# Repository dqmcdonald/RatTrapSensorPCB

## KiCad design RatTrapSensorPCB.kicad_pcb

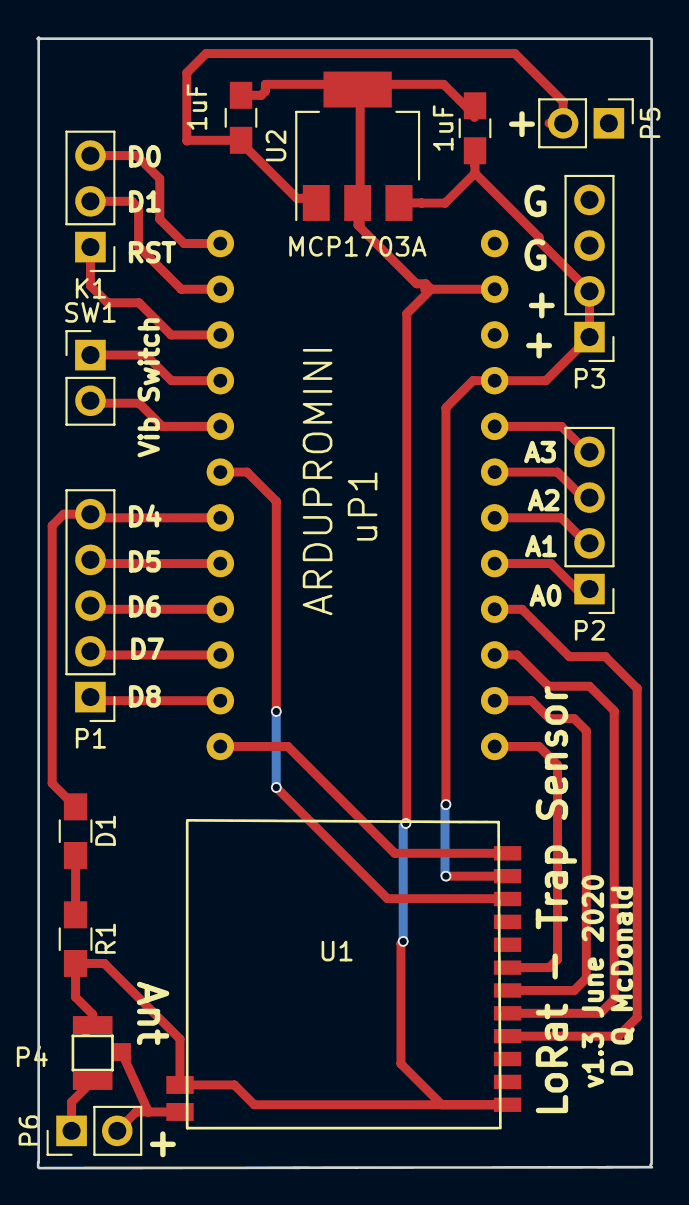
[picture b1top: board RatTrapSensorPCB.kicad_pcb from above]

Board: 2 copper layers, 34.1 x 62.8 mm, 15 parts (0 on the bottom side), 24 nets.

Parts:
1uF, 1uF#2: C; C_0805_HandSoldering
D1: LED; R_0805_HandSoldering
K1: CONN_3; Pin_Header_Straight_1x03_Pitch2.54mm
P1: CONN_5; Pin_Header_Straight_1x05_Pitch2.54mm
P2, P3: CONN_4; Pin_Header_Straight_1x04_Pitch2.54mm
P4: CONN_2; U.Fl_SMD
P5, P6: CONN_2; Pin_Header_Straight_1x02_Pitch2.54mm
R1: 220; R_0805_HandSoldering
SW1: SPST; Pin_Header_Straight_1x02_Pitch2.54mm
U1: LoRaSx1276
U2: MCP1703A; SOT-223-3_TabPin2
uP1: ARDUPROMINI; ArduProMini

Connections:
A0: P2.1, uP1.26
A1: P2.2, uP1.25
A2: P2.3, uP1.24
A3: P2.4, uP1.23
ANT: P4.2, P6.2, U1.13
D0: K1.3, uP1.7
D1: K1.2, uP1.8
D2: SW1.2, uP1.11
D3: U1.10, uP1.12
D4: D1.1, P1.5, uP1.13
D5: P1.4, uP1.14
D6: P1.3, uP1.15
D7: P1.2, uP1.16
D8: P1.1, uP1.17
D9: U1.12, uP1.18
GND: 1uF.2, 1uF#2.2, P3.3, P3.4, P4.1, P5.1, P6.1, R1.2, SW1.1, U1.1, U1.14, U2.2, uP1.10, uP1.20
MISO: U1.5, uP1.28
MOSI: U1.6, uP1.29
NSS: U1.7, uP1.30
unnamed: 1uF.1, P5.2, U2.1
unnamed: D1.2, R1.1
RST: K1.1, uP1.9
SCK: U1.4, uP1.27
V3.3: 1uF#2.1, P3.1, P3.2, U1.11, U2.3, uP1.22

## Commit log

2018-08-07 Added Readme
2018-10-01 Corrected antenna output
2020-05-17 Antenna connection fix
    Fixed error with antenna connections being shorted to ground
2024-10-13 Updated Kicad
